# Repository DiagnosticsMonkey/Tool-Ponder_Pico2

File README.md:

# ReadMe

Ponder - Pico 2 is a varient of Ponder, designed to act as 6, electrically isolated, UART to USB bridges using the Pico 2.
Connect the board to your PC, and be served 6, driverless, COM-ports or ttyACM devices.

## Documentation

Documentation is captured in Markdown and is available in `/docs`, rendered [using docsify here](https://diagnosticsmonkey.github.io/Tool-Ponder_Pico2/#/).

## Design files

All of the design files are included in this repository.

### Hardware

Hardware design files are in [`/hardware`](https://github.com/DiagnosticsMonkey/Tool-Ponder_Pico2/tree/develop/hardware).

Generated outputs such as [Schematic](https://github.com/DiagnosticsMonkey/Tool-Ponder/blob/develop/hardware/outputs/Ponder-Pico2.pdf), [BoM](https://diagnosticsmonkey.github.io/Tool-Ponder_Pico2/#/design?id=bill-of-materials), and [Gerbers](https://github.com/DiagnosticsMonkey/Tool-Ponder_Pico2/tree/develop/hardware/outputs/fab) are all included.

### Software

Nominal software is available TBD.

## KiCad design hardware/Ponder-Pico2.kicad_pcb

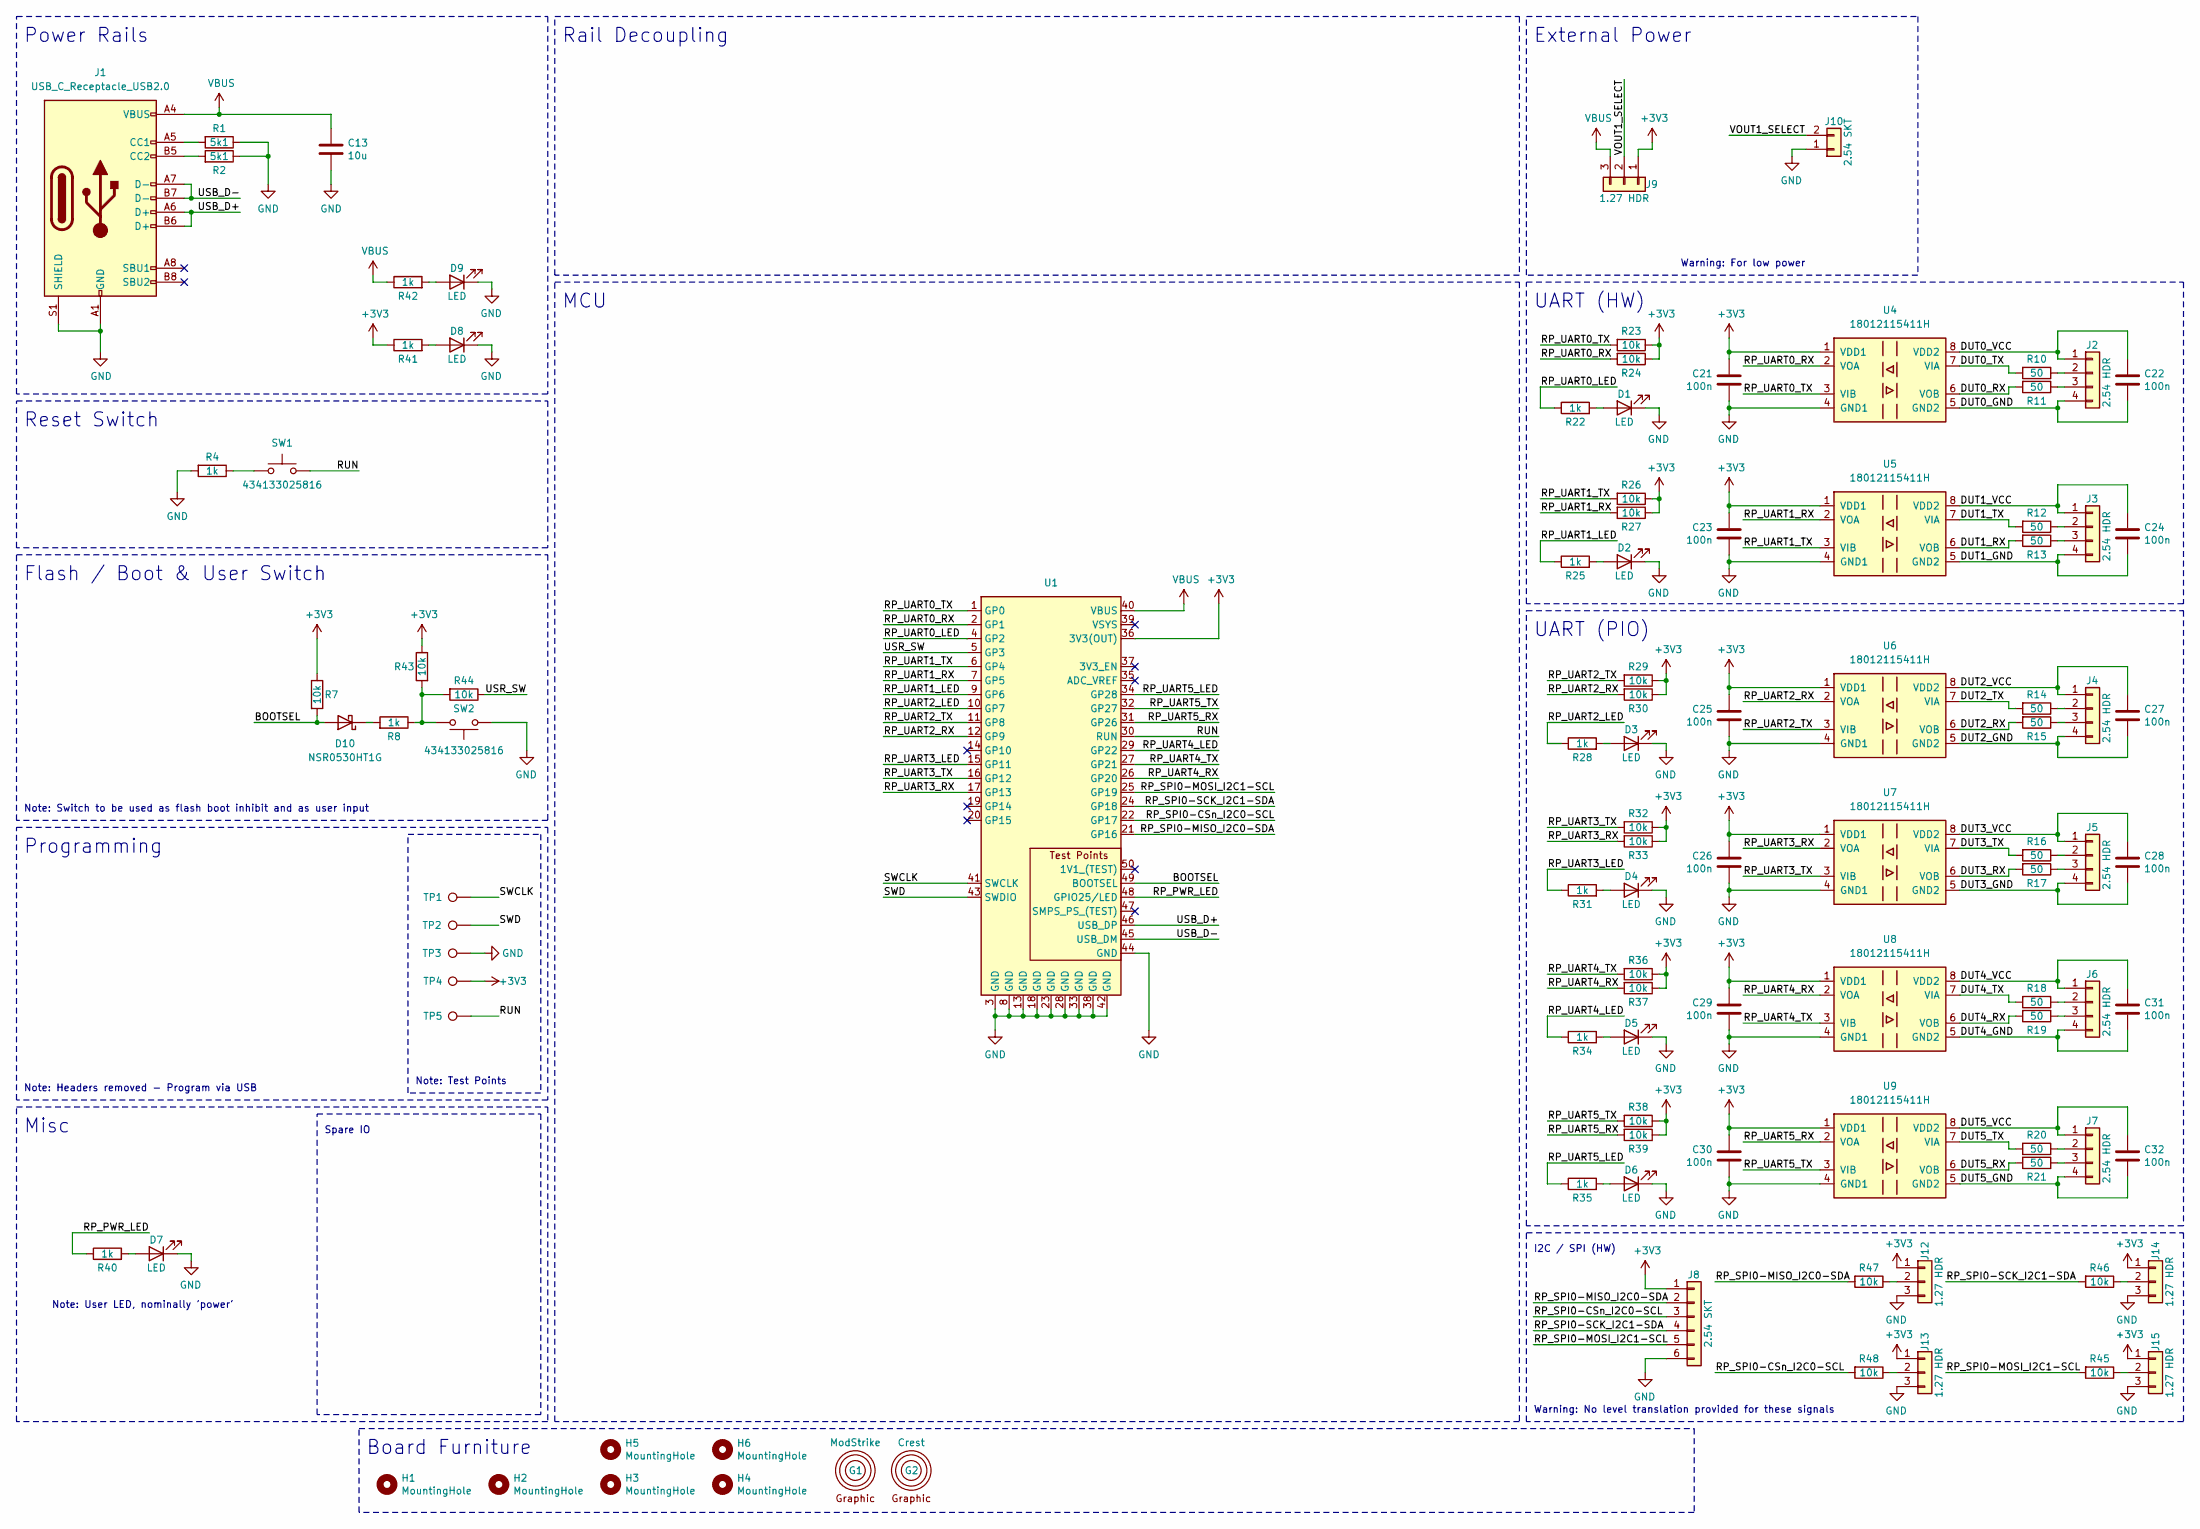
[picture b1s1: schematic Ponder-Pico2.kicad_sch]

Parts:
C13: 10u; C_0805_2012Metric
C21, C22, C23, C24, C25, C26, C27, C28, C29, C30, C31, C32: 100n; C_0402_1005Metric
D1, D2, D3, D4, D5, D6, D7, D8, D9: LED; LED_0603_1608Metric_Pad1.05x0.95mm_HandSolder
D10: NSR0530HT1G; D_SOD-323
G1: ModStrike
G2: Crest; Crest-10mm
H1, H2, H3, H4, H5, H6: MountingHole; MountingHole_2.7mm_M2.5
J1: USB_C_Receptacle_USB2.0; USB_C_Receptacle_GCT_USB4105-xx-A_16P_TopMnt_Horizontal
J2, J3, J4, J5, J6, J7: 2.54 HDR; PinHeader_1x04_P2.54mm_Horizontal
J8: 2.54 SKT; PinSocket_1x06_P2.54mm_Horizontal
J9, J12, J13, J14, J15: 1.27 HDR; PinHeader_1x03_P1.27mm_Vertical
J10: 2.54 SKT; M208890245
R1, R2: 5k1; R_0402_1005Metric
R4, R8, R22, R25, R28, R31, R34, R35, R40, R41, R42: 1k; R_0402_1005Metric
R7, R23, R24, R26, R27, R29, R30, R32, R33, R36, R37, R38, R39, R43, R44, R45, R46, R47, R48: 10k; R_0402_1005Metric
R10, R11, R12, R13, R14, R15, R16, R17, R18, R19, R20, R21: 50; R_0402_1005Metric
SW1, SW2: 434133025816; SW_Push_1P1T_NO_Vertical_Wuerth_434133025816
TP1, TP2, TP3, TP4, TP5: TestPoint; TestPoint_Pad_D1.0mm
U1: RaspberryPi-Pico-SMD-TP
U4, U5, U6, U7, U8, U9: 18012115411H; SOIC-8_3.9x4.9mm_P1.27mm

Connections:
+3V3: C21.1, C23.1, C25.1, C26.1, C29.1, C30.1, J8.1, J9.1, J12.1, J13.1, J14.1, J15.1, R7.1, R23.1, R24.1, R26.1, R27.1, R29.1, R30.1, R32.1, R33.1, R36.1, R37.1, R38.1, R39.1, R41.1, R43.1, TP4.1, U1.36 (3V3(OUT)), U4.1 (VDD1), U5.1 (VDD1), U6.1 (VDD1), U7.1 (VDD1), U8.1 (VDD1), U9.1 (VDD1)
/BOOTSEL: D10.2 (A), R7.2, U1.49 (BOOTSEL)
/DUT0_GND: C22.2, J2.4, U4.5 (GND2)
/DUT0_RX: R11.2, U4.6 (VOB)
/DUT0_TX: R10.2, U4.7 (VIA)
/DUT0_VCC: C22.1, J2.1, U4.8 (VDD2)
/DUT1_GND: C24.2, J3.4, U5.5 (GND2)
/DUT1_RX: R13.2, U5.6 (VOB)
/DUT1_TX: R12.2, U5.7 (VIA)
/DUT1_VCC: C24.1, J3.1, U5.8 (VDD2)
/DUT2_GND: C27.2, J4.4, U6.5 (GND2)
/DUT2_RX: R15.2, U6.6 (VOB)
/DUT2_TX: R14.2, U6.7 (VIA)
/DUT2_VCC: C27.1, J4.1, U6.8 (VDD2)
/DUT3_GND: C28.2, J5.4, U7.5 (GND2)
/DUT3_RX: R17.2, U7.6 (VOB)
/DUT3_TX: R16.2, U7.7 (VIA)
/DUT3_VCC: C28.1, J5.1, U7.8 (VDD2)
/DUT4_GND: C31.2, J6.4, U8.5 (GND2)
/DUT4_RX: R19.2, U8.6 (VOB)
/DUT4_TX: R18.2, U8.7 (VIA)
/DUT4_VCC: C31.1, J6.1, U8.8 (VDD2)
/DUT5_GND: C32.2, J7.4, U9.5 (GND2)
/DUT5_RX: R21.2, U9.6 (VOB)
/DUT5_TX: R20.2, U9.7 (VIA)
/DUT5_VCC: C32.1, J7.1, U9.8 (VDD2)
/RP_PWR_LED: R40.1, U1.48 (GPIO25/LED)
/RP_SPI0-CSn_I2C0-SCL: J8.3, R48.2, U1.22 (GP17)
/RP_SPI0-MISO_I2C0-SDA: J8.2, R47.2, U1.21 (GP16)
/RP_SPI0-MOSI_I2C1-SCL: J8.5, R45.2, U1.25 (GP19)
/RP_SPI0-SCK_I2C1-SDA: J8.4, R46.2, U1.24 (GP18)
/RP_UART0_LED: R22.1, U1.4 (GP2)
/RP_UART0_RX: R24.2, U1.2 (GP1), U4.2 (VOA)
/RP_UART0_TX: R23.2, U1.1 (GP0), U4.3 (VIB)
/RP_UART1_LED: R25.1, U1.9 (GP6); also elsewhere on the board
/RP_UART1_RX: R27.2, U1.7 (GP5), U5.2 (VOA)
/RP_UART1_TX: R26.2, U1.6 (GP4), U5.3 (VIB)
/RP_UART2_LED: R28.1, U1.10 (GP7)
/RP_UART2_RX: R30.2, U1.12 (GP9), U6.2 (VOA)
/RP_UART2_TX: R29.2, U1.11 (GP8), U6.3 (VIB)
/RP_UART3_LED: R31.1, U1.15 (GP11)
/RP_UART3_RX: R33.2, U1.17 (GP13), U7.2 (VOA)
/RP_UART3_TX: R32.2, U1.16 (GP12), U7.3 (VIB)
/RP_UART4_LED: R34.1, U1.29 (GP22)
/RP_UART4_RX: R37.2, U1.26 (GP20), U8.2 (VOA)
/RP_UART4_TX: R36.2, U1.27 (GP21), U8.3 (VIB)
/RP_UART5_LED: R35.1, U1.34 (GP28)
/RP_UART5_RX: R39.2, U1.31 (GP26), U9.2 (VOA)
/RP_UART5_TX: R38.2, U1.32 (GP27), U9.3 (VIB)
/RUN: SW1.2, TP5.1, U1.30 (RUN)
/SWCLK: TP1.1, U1.41 (SWCLK)
/SWD: TP2.1, U1.43 (SWDIO)
/USB_D+: J1.A6 (D+), J1.B6 (D+), U1.46 (USB_DP)
/USB_D-: J1.A7 (D-), J1.B7 (D-), U1.45 (USB_DM)
/USR_SW: R44.1, U1.5 (GP3)
/VOUT1_SELECT: J9.2, J10.2
GND: C13.2, C21.2, C23.2, C25.2, C26.2, C29.2, C30.2, D1.1 (K), D2.1 (K), D3.1 (K), D4.1 (K), D5.1 (K), D6.1 (K), D7.1 (K), D8.1 (K), D9.1 (K), J1.A1 (GND), J1.A12 (GND), J1.B1 (GND), J1.B12 (GND), J1.S1 (SHIELD), J8.6, J10.1, J12.3, J13.3, J14.3, J15.3, R1.1, R2.1, R4.2, SW2.2, TP3.1, U1.3 (GND), U1.8 (GND), U1.13 (GND), U1.18 (GND), U1.23 (GND), U1.28 (GND), U1.33 (GND), U1.38 (GND), U1.42 (GND), U1.44 (GND), U4.4 (GND1), U5.4 (GND1), U6.4 (GND1), U7.4 (GND1), U8.4 (GND1), U9.4 (GND1)
unnamed: D1.2 (A), R22.2
unnamed 58: D2.2 (A), R25.2; also elsewhere on the board
unnamed: D3.2 (A), R28.2
unnamed: D4.2 (A), R31.2
unnamed: D5.2 (A), R34.2
unnamed: D6.2 (A), R35.2
unnamed: D7.2 (A), R40.2
unnamed: D8.2 (A), R41.2
unnamed: D9.2 (A), R42.2
unnamed: D10.1 (K), R8.2
unnamed: J1.A5 (CC1), R1.2
unnamed: J1.B5 (CC2), R2.2
unnamed: J2.2, R10.1
unnamed: J2.3, R11.1
unnamed: J3.2, R12.1
unnamed: J3.3, R13.1
unnamed: J4.2, R14.1
unnamed: J4.3, R15.1
unnamed: J5.2, R16.1
unnamed: J5.3, R17.1
unnamed: J6.2, R18.1
unnamed: J6.3, R19.1
unnamed: J7.2, R20.1
unnamed: J7.3, R21.1
unnamed: J12.2, R47.1
unnamed: J13.2, R48.1
unnamed: J14.2, R46.1
unnamed: J15.2, R45.1
unnamed: R4.1, SW1.1
unnamed: R8.1, R43.2, R44.2, SW2.1
VBUS: C13.1, J1.A4 (VBUS), J1.A9 (VBUS), J1.B4 (VBUS), J1.B9 (VBUS), J9.3, R42.1, U1.40 (VBUS)

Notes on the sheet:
Warning: No level translation provided for these signals
UART (PIO)
Misc
Note: Switch to be used as flash boot inhibit and as user input
Flash / Boot & User Switch
Spare IO
Board Furniture
Rail Decoupling
Note: Test Points
Note: User LED, nominally 'power'
Note: Headers removed - Program via USB
External Power
UART (HW)
I2C / SPI (HW)
MCU
Warning: For low power
Reset Switch
Programming
Power Rails

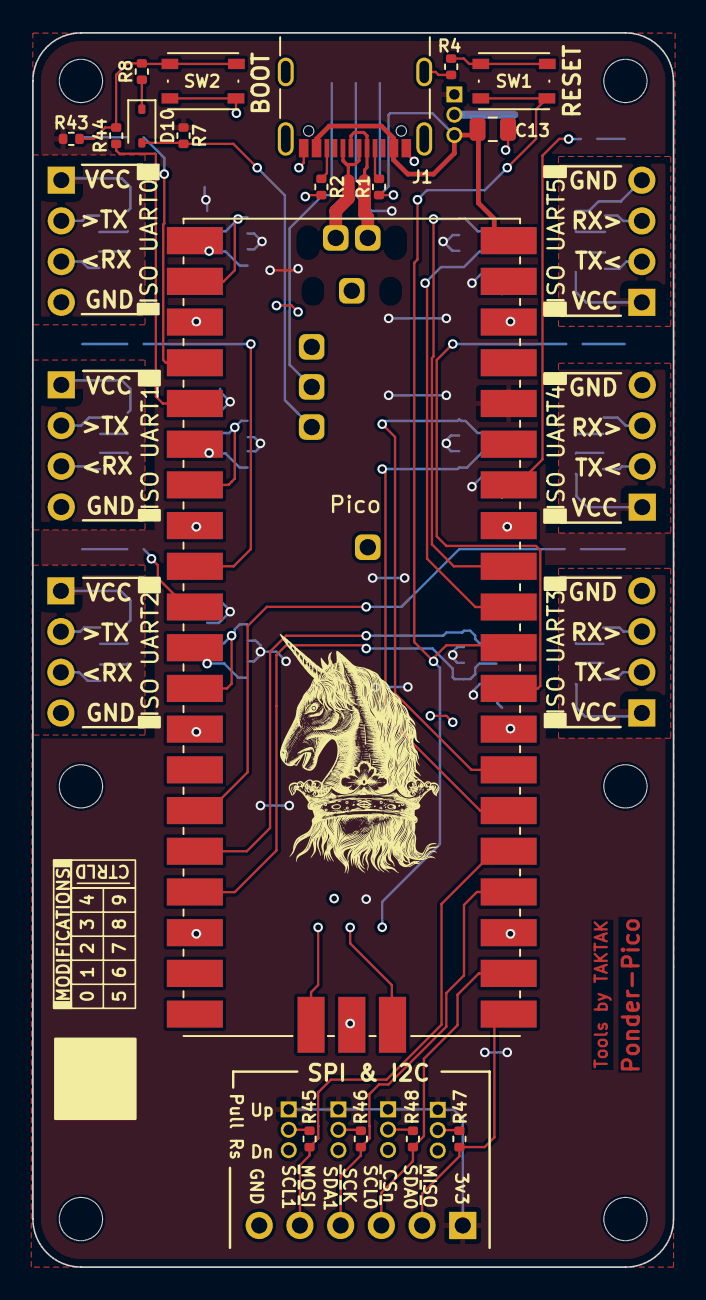
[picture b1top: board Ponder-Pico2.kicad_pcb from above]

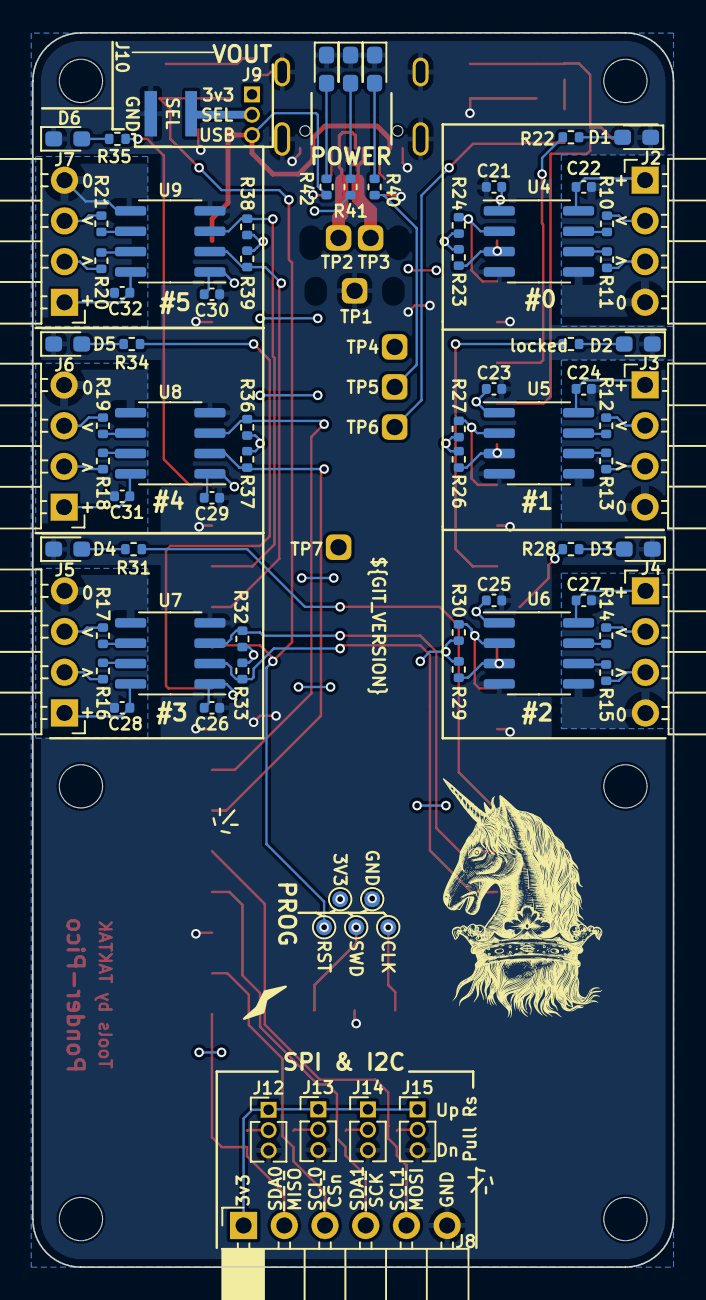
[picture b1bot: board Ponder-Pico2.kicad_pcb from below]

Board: 2 copper layers, 40.0 x 77.0 mm, 103 parts (79 on the bottom side), 88 nets.

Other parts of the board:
locked: 1k; R_0402_1005Metric

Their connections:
/RP_UART1_LED: locked.1; also elsewhere on the board
unnamed 58: locked.2; also elsewhere on the board

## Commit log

2024-09-03 Adding kicad template @7c4f6e5
2024-09-03 Updating template for project
2024-09-03 Description slug was too long
2024-09-03 Adding baseline MCU and supportive blocks
2024-09-03 Adding basline docsify template and populating initial info for Ponder
2024-09-03 Correcting redirect on repo slug
2024-09-09 Adding programming headers, some testpoints, and minimal MCU fanout with power
2024-09-09 Checking border update script
2024-09-09 Adding 3d models of parts
2024-09-09 Fixing board outline, aligning USB connector to board edge, clearing some early DRC errors
2024-09-10 Adding modstrike box
2024-09-10 Adding ISOs and 4P headers
2024-09-10 Changing step file used for ISO
2024-09-10 Adding pull-ups and LEDs for UARTs. Added nominal I2C and SPI connector along with startes of some selectable off-board low power headers
2024-09-10 Updating boarder props via script
2024-09-10 Adding LEDs for power status
2024-09-10 Tittivating connector legends
2024-09-10 Minor tweaks an bit of layout
2024-09-11 Swapping flash in sch for part which isn't the size of a small exoplanet
2024-09-11 First pass layout
2024-09-11 Silk tittivating
2024-09-11 C15 & 16 RefDes had escaped the box when changing footprint
2024-09-11 Re-routing temporarily shelved items. Fixing DRC
2024-09-12 Border update and exclusions
2024-09-12 Aligning noconnects
2024-09-12 Pushing updated sch to git
2024-09-16 Adding version fields and silk elements
2024-09-16 Prepping script for RC tag
2024-09-16 Updated borders, generated outputs for review. N.B. this applies and must be manually checked each time: https://gitlab.com/kicad/code/kicad/-/issues/14360
2024-09-17 Unifying vias to single drill. Adding some plane connections
2024-09-17 Preparing script for release
2024-09-17 Updating borders and version info for release. Generated output files
2024-09-17 Adding starters of documentation
2024-09-17 Wording tweak
2024-09-17 Updating frontpage and adding holding page for purchase
2024-09-18 Adding futher detail to documentation
2024-09-30 Typo on schematic filename
2024-10-30 Adding start of Pico 2 variant for Ponder
2024-10-30 Modifying Pico footprint for USB holes to match DS
2024-10-30 script update prior to tagging
2024-10-30 Template update
2024-10-30 Generated outputs for 1.0, including layout bug on silk property
2024-10-30 Linking correct model to footprint
2024-10-30 Quick cut of docs for Pico 2 variant
2024-10-30 Incorrectly cross-referencing to Ponder. Also changed silk and mask colour
2024-10-30 Fix board lighting issue in images and swap for black mask
2024-12-03 Assy imagery
